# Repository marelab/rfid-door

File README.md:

# ESP8266 RFID - Access Control with Wiegand Protocol powerd by Door Bell transformer 8-12V AC or DC

## First of all 
big thanks to the [ESP-RFID Project](https://github.com/esprfid/esp-rfid) with the work they have done. The "rfid-door" hardware is 100% compatible with their software also a modified [Firmware](https://github.com/marelab/esp-rfid/releases) with extended MQTT support is included with the marelab RFID-DOOR Version that can be used. Just the hardware design is differnt in my version. The RFID-DOOR pcb is designed to be powered directly from the AC Ring Bell transformer (8-12V AC). But can also be configured to use a 8-12V DC power by just solder bridges. Main reason why I used a different design was the fact that I didn't wanted to setup a new DC source and cables for that device, it can be integrated without any extra power infrastructure. Most german households have a AC Ringbell with 8 or 12V transformer next to the door. 

## RFID-DOOR
 
 NFC/RFID WIFI Access Control hardware interfacing a cheap MFRC522, PN532 RFID, RDM6300 readers or Wiegand RFID readers with a Espressif's ESP8266 Microcontroller as Wifi Bridge to drive the door open coil to unlock a home door and to include it into a home automatisation system. The pcb is designed with [KiCad](http://kicad.org/) an opensoure EDA System. Ready Gerber Files can be found under Gerber. Plz use the Version Tab for download the newest Release the Master Branch includes the current development stage! 

## Differnces of the ESP-RFID Hardware to RFID-DOOR Hardware
The marelab RFID-DOOR hardware: 
```
* Can be powered by AC RingBell transformer directly no seperate power source need at the installation spot
* No mechanical Relais just Silicon Door coil is driven by smal opto mosfet
* Currentlimitation of the door coil to limit the current breakdown while magentic lock is activated  
* 5V kompatible Wiegand DO/D1 Lines as default
```

## Features
### For Users
* Minimal effort for setting up your Access Control system, just flash and everything can be configured via Web UI
* Capable of managing up to 1.000 Users (even more is possible)
* Great for Maker Spaces, Labs, Schools, etc
* Cheap to build and easy to maintain
### For Tinkerers
* Open Source (minimum amount of hardcoded variable, this means more freedom)
* Using WebSocket protocol to exchange data between Hardware and Web Browser
* Data is encoded as JSON object
* Records are Timestamped (Time synced from a NTP Server)
* MQTT enabled for using by Smart Home automatisation.
* Bootstrap, jQuery, FooTables for beautiful Web Pages for both Mobile and Desktop Screens
* Thanks to ESPAsyncWebServer Library communication is Asynchronous
### Official Hardware
* Small size form factor just 4,5cm * 4,5 cm
* Single power source (Ring Bell transformer) for RFID-DOOR hardware & RFID Wiegand Reader and magnetic lock for opening doors.
* Exposed programming pins for ESP8266
* Regarding hardware design, you get multiple possible setup options:
* Forward Bell ringing on reader to MCU or pass it out of board
* Control reader’s status LED
* Control reader’s status BUZZER sound *
* Power reader, lock and the board through single 8V, AC Ring Bell Transformer
* Power for Magnetic Lock / Door Relais is supplied by RFID-DOOR Hardware
* Possible to use any kind and any type of Wiegand readers
* Smart Home integration over MQTT
* Fits in an universal enclosures with DIN mount
* Open Source Hardware

## Getting Started
New features (and also bugs) are introduced often and some functions may become deprecated. Please feel free to comment or give feedback.

### Standard Door Bell Setup

### RFID-DOOR integrated into Door Bell Setup

## Hardware you need

### Hardware
* [marelab RFID-DOOR Board](https://www.marelab.org/index.php/smarthome-iot/rfid-door) can be ordered here
* A MFRC522 RFID PCD Module or PN532 NFC Reader Module or RDM6300 125KHz RFID Module Wiegand based RFID reader
* n quantity of Mifare Classic 1KB (recommended due to available code base) PICCs (RFID Tags) equivalent to User Number
* A door Relay 8-12V
* A Ringbell Transformer 8-12V 

### Software you need
* Get the latest hardware release from [here.](https://github.com/marelab/rfid-door/releases)
* Get the firmware software from [here.](https://github.com/marelab/esp-rfid/releases)
* See Building [Building](https://github.com/marelab/rfid-door#building)
* See [Security](https://github.com/marelab/esp-rfid#security) for your safety.
* See [ChangeLog](https://github.com/marelab/esp-rfid/blob/dev/CHANGELOG.md)

### Setup & get it running 
* First, flash firmware (you can use /bin/flash.bat on Windows) to your ESP either using Arduino IDE or with your favourite flash tool
* (optional) Fire up your serial monitor to get informed
* Search for Wireless Network "esp-rfid-xxxxxx" and connect to it (It should be an open network and does not require password)
* Open your browser and type either "http://192.168.4.1" or "http://esp-rfid.local" (.local needs Bonjour installed on your computer) on address bar.
* Log on to ESP, default password is "admin"
* Go to "Settings" page
* Configure your amazing access control device. Push "Scan" button to join your wireless network, configure RFID hardware, Relay Module.
* Save settings, when rebooted your ESP will try to join your wireless network.
* Check your new IP address from serial monitor and connect to your ESP again. (You can also connect to "http://esp-rfid.local")
* Go to "Users" page
* Scan a PICC (RFID Tag) then it should glimpse on your Browser's screen.
* Type "User Name" or "Label" for the PICC you scanned.
* Choose "Allow Access" if you want to
* Click "Add"
* Congratulations, everything went well, if you encounter any issue feel free to ask help on GitHub.

### RFID-DOOR Connectors

| Number | Function                                     | ESP8266           |
|-------:|:--------------------------------------------:|:------------------|
| 1      | DoorR / Magnetic Look / Door Relais Conector |    -              |
| 2      | DoorR / Magnetic Look / Door Relais Conector |    -              |
| 3      | 12V out / 12V+ DC                            |    -              |
| 4      | D0 Wiegand D0                                | GPIO-04*          |
| 5      | D1 Wiegand D1                                | GPIO-05*	        |
| 6      | LED                                          | GPIO-05           |
| 7      | W26                                          | GPIO-05           |
| 8      | BUZ                                          | GPIO-05           |
| 9      | GND                                          |    -              |
| 10     | GND                                          |    -              |
| 11     | 12V AC                                       |    -              |
| 12     | 12V AC                                       |    -              |
| 13     | JP4 Reset                                    | GPIO-05           |
| 14     | JP5 Firmware Upload enable                   | GPIO-05           |
|        | JP3-1 3,3V Serial Connector to ESP8266       |                   |
|        | JP3-2 TX Serial Connector to ESP8266         | GPIO-05           |
|        | JP3-3 RX Serial Connector to ESP8266         | GPIO-05           |
|        | JP3-4 GND Serial Connector to ESP8266        | GPIO-05           |

(*) 5V In/Output Signal

### RFID-DOOR Functional Blocks

| Letter | Hardware Function Block                                                                                             | 
|-------:|:-------------------------------------------------------------------------------------------------------------------:|
| A      | Switches the Magnetic Lock/Door Relais by Opto Mosfet and 2W Magnetic Lock Resistor that limits starting current    |
| B      | 3,3V Linear Driver for ESP8266 supply                                                                               | 
| C      | Diode Bridge & Self Resetable Fuse for converting AC to DC Ripple power. The Cxx Cap is decoupled by a the Diode Dxx if the 12V of the Bridge falls down for ms while the magnetic lock is used it delivers the energy for the 5V stage  | 
| D      | 5V StepDown Converter that powers (B) and the MosFet for (E)                                                        | 
| E      | In / Out 3,3V Signal Lines ESP to 5V on Conector 

## **Building** & Setup Hardware

#### The AC Ring Bell Transformer
Be carefull with 12V AC Ring bell transformers. The DC Voltage after the Diode bridge can be around 18V DC!!! That will not kill the RFID-DOOR hardware but it will kill a 12V RFID Reader that is connected to the RFID-DOOR. Why is that happening most Readers have a build in AMS1117 Voltage regulator wich has a maximum 16V input. The RFID-DOOR transforms the AC input Voltage in three stages first Stage is a diode bridge to transform AC to rippled DC then a Step Down Regulator generates 5V DC that can handle 24V DC input next the 5V is converted to 3,3V with a AMS1117 for the ESP. The RFID-DOOR won't get killed because the AMS1117 lives behind the 5V StepDown stage. The Rippled DC is connected directly to the power reader connectors. 
The easiest way to get around that problem is using a 8V AC Ringbell transformer. For example someting like this:

Just use the 8V instead of 12V. The rippled DC after the Diode Bridge is around 14-15V and in the range a AMS1117 of the Reader can handle.
Just for details about german standard and regulations for the bell transformer that has to be used. https://de.wikipedia.org/wiki/Klingeltransformator

####  Placing the ACT4088 IC
The ACT4088 Step Down is a quite tiny part and its quite inpossible to indetify Pin1 without a mircoscope or strong lense. As hint thats a picture of the ACT4088 to find Pin1 as marked in the image.

#### Cad drawing 

The Encloser drill holes dimension is 2,5 mm

#### Special Configuration solder bridges
The board can be customized for special needs if you don't want or have a standard configuration. Some solder Bridges see the pictures of the PCB Back & Top where to find them can configure direct 12V DC Input and or disable the 5V Stage for the D0 / D1 pins. 

!!!Warning all described here might disable some safety features of the board so you should totaly know what you are doing using this!!!

```
##### 12V DC Power Input
If your power source is 12V DC you don't need the Diode Bridge and the 
Capacitor Cxx to be soldered on the board. Solder the JP1 and JP2 
Solder Bridge Jumpers  
```

```
##### 3,3V DO / D1 Wiegand Interface
If you don't need a 5V TTL compatble In/Out of the D1/D0 Lines just 
solder the Solder Bridges JP7/JP8. Don't solder then the Mosfets Q1 & 
Q2 as well as the four Resistors Rxx,Rxx,Rxx,Rxx. 
```

```
##### Bridge the Magnetic Lock / Door Relais current limitation 
By solder the JP3 Bridge the R1 2W Resistor is bridged and so no current 
limitation of a starting magentic coil / Door Lock saves the MosFet!!! 
The R1 Resitor don't need to be solderd anymore. 
```

## Software

#### Wich firmware should I use?
If you want to have a smart home integration or want to manage more then one Door I would recomend the marelab version, because of the extended MQTT functions and multi device support.
Otherwise you can use also the orginal firmware from the ESP-RFID Project. 

#### Using Compiled Binaries
Download compiled binaries from GitHub Releases page:
marelab modified firmware with extended MQTT support https://github.com/marelab/esp-rfid/releases 
or the orignal firmware from https://github.com/esprfid/esp-rfid/releases

#### Flashing the device
For a selfmade NF-DOOR pcb you need a USB to serial Bridge to flash the first Version. New Firmware Versions can then be updated by OTA (Over the Air Wifi Update) done with the web gui.
If you bought the RFID-DOOR Hardware the ESP is already programmed with the firmware so you don't need the USB to serial adapter for flashing.
On Windows you can use **"flash.bat"**, it will ask you which COM port that ESP is connected and then flashes it. You can use any flashing tool and do the flashing manually. The flashing process itself has been described at numerous places on Internet.

#### Self building With PlatformIO
##### Backend
The build environment is based on [PlatformIO](http://platformio.org). Follow the instructions found here: http://platformio.org/#!/get-started for installing it but skip the ```platform init``` step as this has already been done, modified and it is included in this repository. In summary:

```
sudo pip install -U pip setuptools
sudo pip install -U platformio
git clone https://github.com/esprfid/esp-rfid.git
cd esp-rfid
platformio run
```

When you run ```platformio run``` for the first time, it will download the toolchains and all necessary libraries automatically.

##### Debug information
When you compiling and flashing a debug Version the ESP sends Debug Messages over the Serial Port thats usefull for trace and test purpose.

##### Useful commands:

* ```platformio run``` - process/build all targets
* ```platformio run -e generic -t upload``` - process/build and flash just the ESP12e target 
* ```platformio run -e debug -t upload``` - process/build and flash just the ESP12e target 
* ```platformio run -t clean``` - clean project (remove compiled files)

The resulting (built) image(s) can be found in the directory ```/bin``` created during the build process.

##### Frontend
You can not simply edit Web UI files because you will need to convert them to C arrays, which can be done automatically by a gulp script that can be found in tools directory or you can use compiled executables at the same directory as well (for Windows PCs only).

If you want to edit esp-rfid's Web UI you will need (unless using compiled executables):
* NodeJS
* npm (comes with NodeJS installer)
* Gulp (can be installed with npm)

Gulp script also minifies HTML and JS files and compresses (gzip) them. 

In order to test your changes without flashing the firmware you can launch websocket emulator which is included in tools directory.
* You will need to Node JS for websocket emulator.
* Run ```npm update``` to install dependencies
* Run emulator  ```node wserver.js```
* then you will need to launch your browser with CORS disabled:
* ```chrome.exe --args --disable-web-security -–allow-file-access-from-files --user-data-dir="C:\Users\USERNAME"```

Get more information here: https://stackoverflow.com/questions/3102819/disable-same-origin-policy-in-chrome

### Pin Layout

The following table shows the typical pin layout used for connecting readers hardware to ESP:

| ESP8266 | NodeMcu/WeMos | Wiegand | PN532 | MFRC522 | RDM6300 | 
|--------:|:-------------:|:-------:|:-----:|:-------:|:-------:|
| GPIO-15 | D8            |         | SS    | SDA/SS  |         |
| GPIO-13 | D7            | D0      | MOSI  | MOSI    |         |
| GPIO-12 | D6            | D1      | MISO  | MISO    |         |
| GPIO-14 | D5            |         | SCK   | SCK     | TX      |
| GPIO-04 | D2            |         |       |         |         |
| GPIO-05 | D1            |         |       |         |         |

For Wiegand based readers, you can configure D0 and D1 pins via settings page. By default, D0 is GPIO-4 and D1 is GPIO-5

## Time
We are syncing time from a NTP Server (in Client -aka infrastructure- Mode). This will require ESP to have an Internet connection. Additionally your ESP can also work without Internet connection too (Access Point -aka Ad-Hoc- Mode),  without giving up functionality.
This will require you to do syncing manually. ESP can store and hold time for you approximately 51 days without a major issue, device time can drift from actual time depending on usage, temperature, etc.
So you have to login to settings page and sync it in a timely fashion.

## **Security**
We assume **ESP-RFID** project -as a whole- does not offer strong security. There are PICCs available that their UID (Unique Identification Numbers) can be set manually (Currently esp-rfid relies only UID to identify its users). Also there may be a bug in the code that may result free access to your belongings. And also, like every other network connected device esp-rfid is vulnerable to many attacks including Man-in-the-middle, Brute-force, etc.

This is a simple, hobby grade project, do not use it where strong security is needed.

What can be done to increase security? (by you and by us)

* We are working on more secure ways to Authenticate RFID Tags.
* You can disable wireless network to reduce attack surface. (This can be configured in Web UI Settings page)
* Choose a strong password for the Web UI

## Scalability
Since we are limited on both flash and ram size things may get ugly at some point in the future. You can find out some test results below.

## License
The code parts are licensed under [MIT License](https://github.com/esprfid/esp-rfid/blob/stable/LICENSE), 3rd party libraries that are used by this project are licensed under different license schemes, please check them out as well.

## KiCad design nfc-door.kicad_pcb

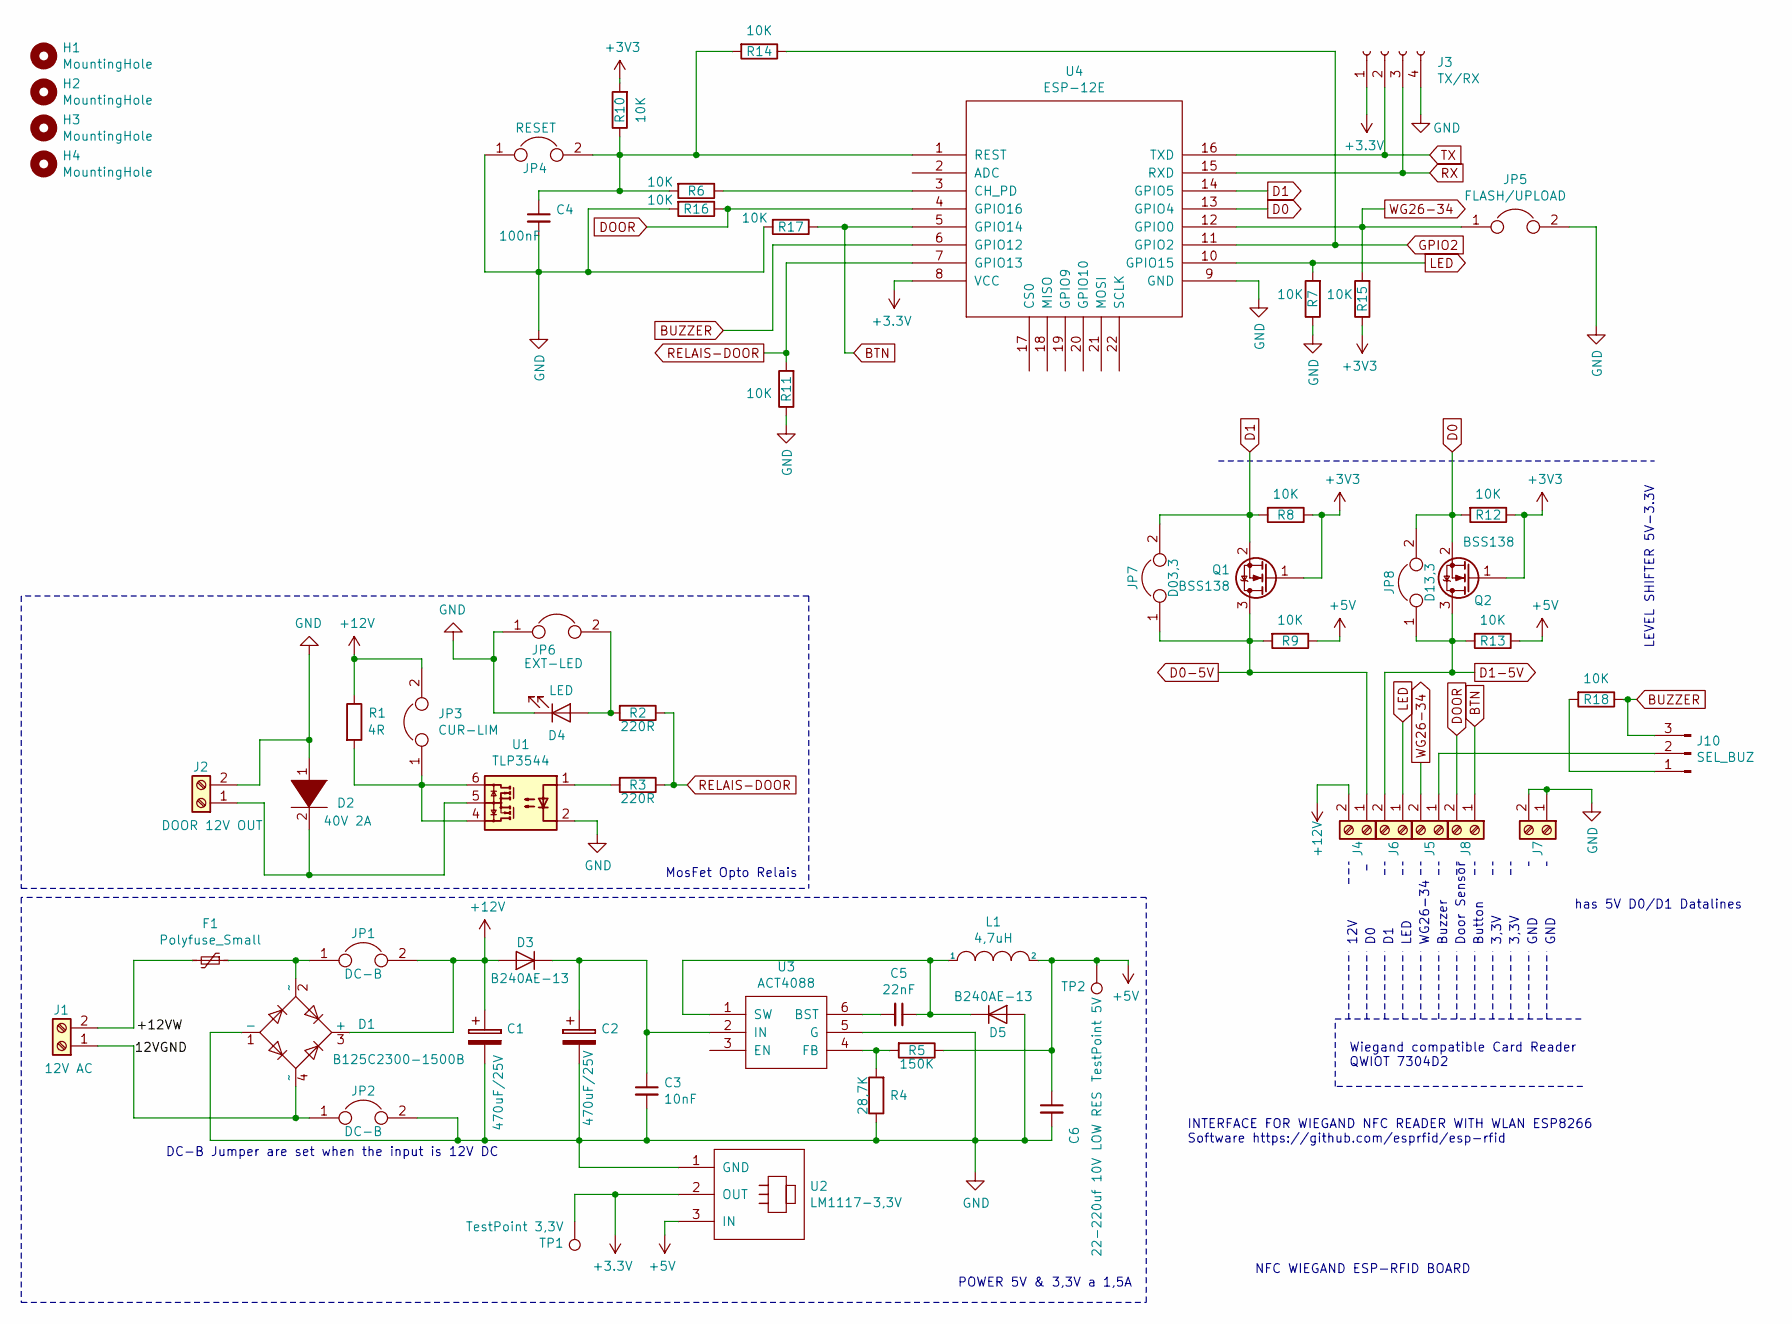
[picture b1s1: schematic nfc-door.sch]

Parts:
C1, C2: 470uF/25V; CP_Radial_D10.0mm_P5.00mm
C3: 10nF; C_0805
C4: 100nF; C_0805
C5: 22nF; C_0805
C6: 22-220uf 10V LOW RES; C_1206
D1: B125C2300-1500B; Diode_Bridge_Round_D8.9mm
D2: 40V 2A; D_1206
D3, D5: B240AE-13; D_SMA_Handsoldering
D4: LED; LED_0805
F1: Polyfuse_Small; Fuse_SMD2920
H1, H2, H3, H4: MountingHole; MountingHole_2.5mm_Pad
J1: 12V AC; RM3.5-CON
J2: DOOR 12V OUT; RM3.5-CON
J3: TX/RX; Pin_Header_Straight_1x04_Pitch2.54mm
J4, J5, J6, J7, J8: RM3.5-CON
J10: SEL_BUZ; Pin_Header_Straight_1x03_Pitch2.54mm
JP1, JP2: DC-B; SolderBridge
JP3: CUR-LIM; SolderBridge
JP4: RESET; Pin_Header_Straight_1x02_Pitch2.54mm
JP5: FLASH/UPLOAD; Pin_Header_Straight_1x02_Pitch2.54mm
JP6: EXT-LED; Pin_Header_Straight_1x02_Pitch2.54mm
JP7: D03,3; SolderBridge
JP8: D13,3; SolderBridge
L1: 4,7uH; Inductor_Taiyo-Yuden_NR-40xx_HandSoldering
Q1, Q2: BSS138; SOT-23
R1: 4R; R_2512_HandSoldering
R2, R3: 220R; R_1206
R4: 28,7K; R_1206
R5: 150K; R_1206
R6, R7, R8, R9, R10, R11, R12, R13, R14, R15, R16, R17, R18: 10K; R_1206
TP1: TestPoint 3,3V; SolderWirePad_single_0-8mmDrill
TP2: TestPoint 5V; SolderWirePad_single_0-8mmDrill
U1: TLP3544; DIP-6_W7.62mm_LongPads
U2: LM1117-3,3V; Pin_Header_Straight_1x03_Pitch2.54mm
U3: ACT4088; SOT-23-6
U4: ESP-12E; ESP-12E_SMD

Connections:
+5V: C6.1, L1.2, R5.1, R9.1, R13.1, TP2.1, U2.3 (IN)
+12V: C1.1, D1.3 (+), D3.2 (A), J4.2, JP1.2, JP3.2, R1.1
BTN: J8.1, R17.1, U4.5 (GPIO14)
BUZZER: J10.3, R18.1, U4.6 (GPIO12)
D0: JP8.2, Q2.2 (S), R12.2, U4.13 (GPIO4)
D0-5V: J4.1, JP7.1, Q1.3 (D), R9.2
D1: JP7.2, Q1.2 (S), R8.2, U4.14 (GPIO5)
D1-5V: J6.2, JP8.1, Q2.3 (D), R13.2
DOOR: J8.2, R16.1, U4.4 (GPIO16)
GND: C1.2, C2.2, C3.2, C4.2, C6.2, D1.1 (-), D2.1 (K), D4.1 (K), D5.2 (A), J2.2, J3.4, J7.1, J7.2, JP2.2, JP4.1, JP5.2, JP6.1, R4.1, R7.1, R11.1, R16.2, R17.2, U1.2, U2.1 (GND), U3.5 (G), U4.9 (GND)
GPIO2: R14.1, U4.11 (GPIO2)
LED: J6.1, R7.2, U4.10 (GPIO15)
unnamed: C2.1, C3.1, D3.1 (K), U3.2 (IN)
unnamed: C4.1, JP4.2, R6.2, R10.1, R14.2, U4.1 (REST)
unnamed: C5.1, D5.1 (K), L1.1, U3.1 (SW)
unnamed: C5.2, U3.6 (BST)
unnamed: D1.2 (~~), F1.1, JP1.1
unnamed: D1.4 (~~), J1.1, JP2.1
unnamed: D2.2 (A), J2.1, U1.5
unnamed: D4.2 (A), JP6.2, R2.2
unnamed: F1.2, J1.2
unnamed: J10.1, R18.2
unnamed: J5.1, J10.2
unnamed: JP3.1, R1.2, U1.4, U1.6
unnamed: R3.2, U1.1
unnamed: R4.2, R5.2, U3.4 (FB)
unnamed: R6.1, U4.3 (CH_PD)
RELAIS-DOOR: R2.1, R3.1, R11.2, U4.7 (GPIO13)
RX: J3.3, U4.15 (RXD)
TX: J3.2, U4.16 (TXD)
WG26-34: J5.2, JP5.1, R15.2, U4.12 (GPIO0)

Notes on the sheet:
Wiegand compatible Card Reader QWIOT 7304D2
GND
12V
has 5V D0/D1 Datalines
LEVEL SHIFTER 5V-3.3V
NFC WIEGAND ESP-RFID BOARD
INTERFACE FOR WIEGAND NFC READER WITH WLAN ESP8266 Software https://github.com/esprfid/esp-rfid
DC-B Jumper are set when the input is 12V DC
POWER 5V & 3,3V a 1,5A
MosFet Opto Relais
LED
WG26-34
Buzzer
Door Sensor
Button
3,3V
GND

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
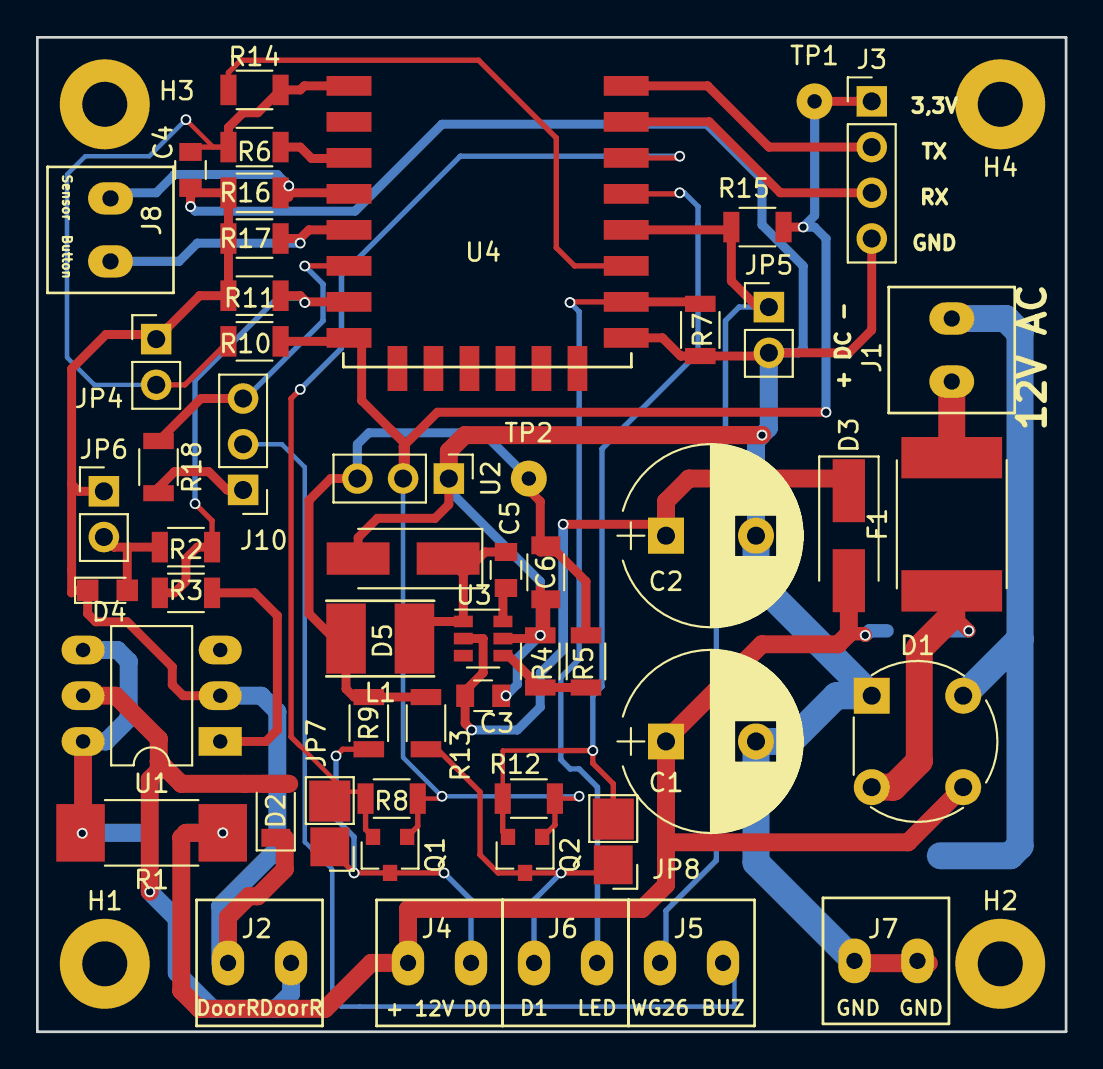
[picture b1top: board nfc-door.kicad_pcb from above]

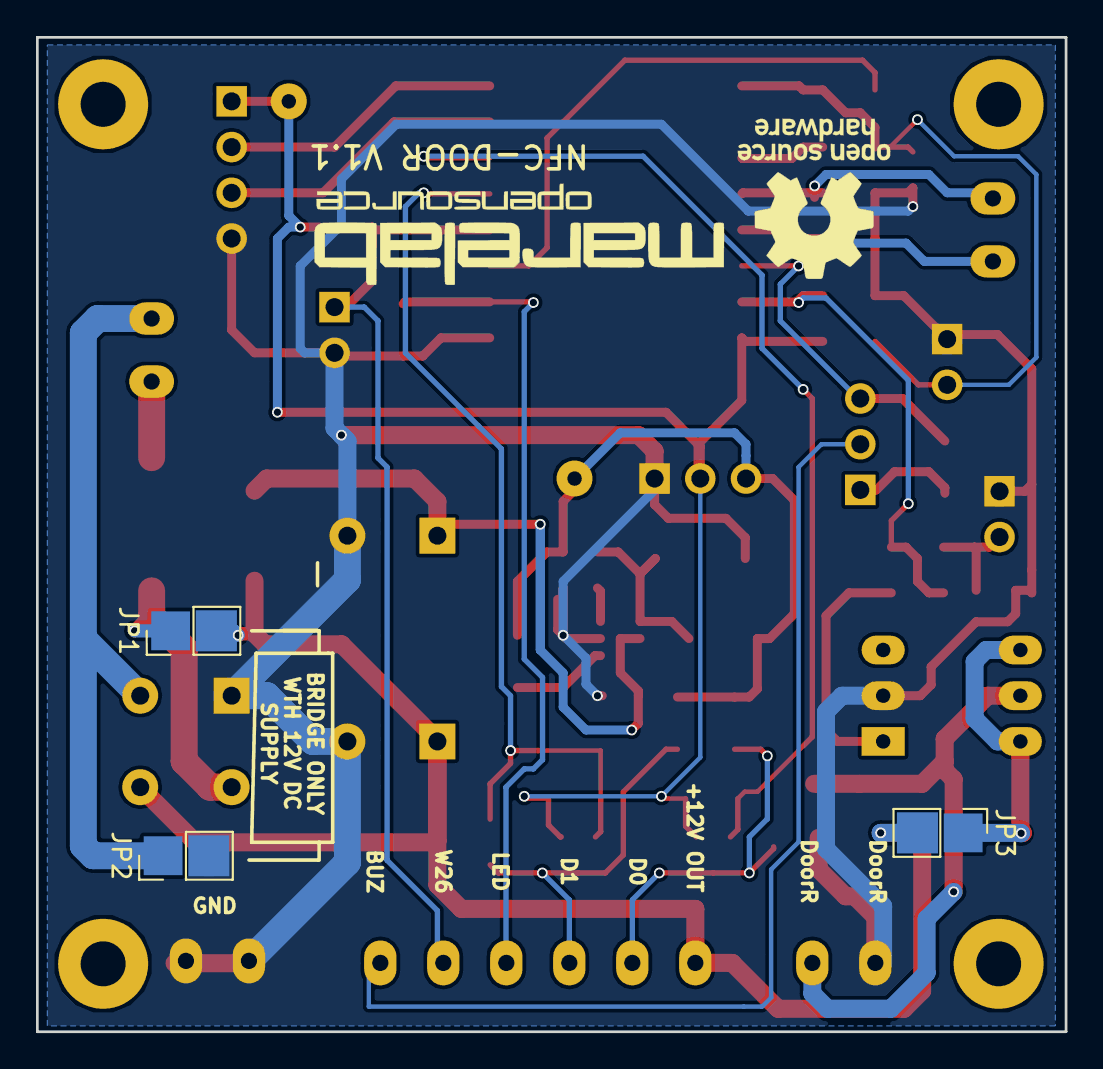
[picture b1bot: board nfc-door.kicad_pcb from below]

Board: 2 copper layers, 57.2 x 55.2 mm, 60 parts (3 on the bottom side), 32 nets.

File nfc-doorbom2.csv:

Pos;Description;Part;Name;Wert;Footprint;Quantity Per PCB;Datasheet;manf-num
1;;C_Small;C4;100nF;C_0805;1;https://www.mouser.de/ProductDetail/Murata-Electronics/GCM21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;CC0805KPX7R8BB104
2;;C_Small;C3;10nF;C_0805;1;;CC0805KRX7R8BB103
3;;C_Small;C6;22-220uf 10V LOW RES ;C_1206;1;;CC0805JRX7R8BB223
4;;C_Small;C5;22nF;C_0805;1;;CC0805JRX7R8BB223
5;Polarized capacitor;CP;C1 C2;470uF/25V;CP_Radial_D10.0mm_P5.00mm;2;https://www.mouser.de/datasheet/2/212/KEM_A4074_ESL-1128319.pdf;ESL477M025AH9
6;Diode symbol for simulation only. Pin order incompatible with official kicad footprints;DIODE;D2; 40V 2A ;D_1206;1;https://www.mouser.de/ProductDetail/AVX/SD1206T040S2R0?qs=sG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;SD1206T040S2R0
7;Silicon Bridge Rectifier, 125V Vrms, 1.5A If, pins=-A+A, SIL-package;B125C2300-1500B;D1;B125C2300-1500B;Diode_Bridge_Round_D8.9mm;1;https://diotec.com/tl_files/diotec/files/pdf/datasheets/b40c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;
8;Diode;D;D3 D5;B240AE-13;D_SMA_Handsoldering;2;https://www.mouser.de/datasheet/2/115/B220AEBE-B245AEBE-1115122.pdf;B240AE-13
9;Light emitting diode;LED;D4;LED;LED_0805;1;~;
10;Resettable fuse, polymeric positive temperature coefficient, small symbol;Polyfuse_Small;F1;Polyfuse_Small;Fuse_SMD2920;1;https://www.mouser.de/ProductDetail/Bel-Fuse/0ZCF0200AF2C?qs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;0ZCF0200AF2C
11;Generic screw terminal, single row, 01x02;Screw_Terminal_01x02;J4 J5 J6 J7 J8;;RM3.5-CON;5;~;
12;Generic screw terminal, single row, 01x02;Screw_Terminal_01x02;J1;12V AC;RM3.5-CON;1;~;
13;Generic screw terminal, single row, 01x02;Screw_Terminal_01x02;J2;DOOR 12V OUT;RM3.5-CON;1;~;
14;Generic connector, single row, 01x03, script generated (kicad-library-utils/schlib/autogen/connector/);Conn_01x03_Male;J10;SEL_BUZ;Pin_Header_Straight_1x03_Pitch2.54mm;1;~;
15;Generic connector, single row, 01x04, script generated (kicad-library-utils/schlib/autogen/connector/);Conn_01x04_Female;J3;TX/RX;Pin_Header_Straight_1x04_Pitch2.54mm;1;~;
16;Jumper, normally closed;Jumper;JP3;CUR-LIM;SolderBridge;1;~;
17;Jumper, normally closed;Jumper;JP7;D03,3;SolderBridge;1;~;
18;Jumper, normally closed;Jumper;JP8;D13,3;SolderBridge;1;~;
19;Jumper, normally closed;Jumper;JP1 JP2;DC-B;SolderBridge;2;~;
20;Jumper, normally closed;Jumper;JP6;EXT-LED;Pin_Header_Straight_1x02_Pitch2.54mm;1;~;
21;Jumper, normally closed;Jumper;JP5;FLASH/UPLOAD;Pin_Header_Straight_1x02_Pitch2.54mm;1;~;
22;Jumper, normally closed;Jumper;JP4;RESET;Pin_Header_Straight_1x02_Pitch2.54mm;1;~;
23;Capacitor symbol for simulation only;INDUCTOR;L1;4,7uH;Inductor_Taiyo-Yuden_NR-40xx_HandSoldering;1;SRN4026-4R7M;SRN4026-4R7M
24;50V Vds, 0.22A Id, N-channel MOSFET, SOT-23;BSS138;Q1 Q2;BSS138;SOT-23;2;https://www.fairchildsemi.com/datasheets/BS/BSS138.pdf;BSS138
25;;R;R6 R7 R8 R9 R10 R11 R12 R13 R14 R15 R16 R17 R18;10K;R_0805;13;;
26;;R;R5;150K;R_1206;1;;
27;;R;R2 R3;220R;R_1206;2;;
28;;R;R4;28,7K;R_1206;1;;
29;;R;R1;4R;R_2512_HandSoldering;1;https://www.mouser.de/ProductDetail/TE-Connectivity-Neohm/CR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;
30;5V StepDown Wandler;ACT4088;U3;ACT4088;SOT-23-6;1;;ACT4088US-T
31;ESP8266 ESP-12E module, 22 pins, 2mm, PCB antenna;ESP-12E;U4;ESP-12E;ESP-12E_SMD;1;http://l0l.org.uk/2014/12/esp8266-modules-hardware-guide-got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;
32;3,3V 1.5A CHINA MODUL;LM1117-3,3V;U2;LM1117-3,3V;Pin_Header_Straight_1x03_Pitch2.54mm;1;;
33;Photo MOSFET optically coupled, ON 3.5A, 60mohm, OFF state 40V, Isolation 2500 VRMS, DIP-6;TLP3544;U1;TLP3544;DIP-6_W7.62mm_LongPads;1;https://toshiba.semicon-storage.com/info/docget.jsp?did=1266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;TLP3544(F)

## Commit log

2019-05-03 Initial V1.1 Version
2019-05-03 Starting ReadMe.md
2019-05-04 Init Version
2019-05-04 overview NFC-DOOR install
2019-05-04 Graphic added
2019-05-14 V1.1 Version
    Version V1.1
    * Corrected Diode Bridge
    * 1206 22uF CAP
2019-05-16 Update Cleaned up Repro
2019-05-16 Schematic & 3D png/pdf
2019-05-16 ACT4088 oriantation
2019-05-16 Update Release
2019-05-16 Firmware to choose from
2019-05-16 Changes to links
2019-05-16 Adding debug build info
2019-05-16 Update Description
2019-05-16 Added pcb pic
2019-05-16 Basic & RFID Setup Grafic
2019-05-16 Images standard & NFC-DOOR setup
2019-05-17 renaming to rfid-door
2019-05-17 Update and grafics Connectors & Overview
2019-05-17 Added Connector Table
2019-05-17 Added Top & Back PCB images
2019-05-17 Special Configuration over Solder Bridges
2019-05-17 Added Demension grafic
2019-05-17 Some cleanUp
2019-05-17 Logo grafics added
2019-05-17 update logo
2019-05-17 Logo update
2021-11-08 Update README.md
    https://forum.kicad.info/t/warning-avoid-all-links-to-kicad-pcb-org-use-kicad-org/31521

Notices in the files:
README.md:
License:
The code parts are licensed under [MIT License](https://github.com/esprfid/esp-rfid/blob/stable/LICENSE), 3rd party libraries that are used by this project are licensed under different license schemes, please check them out as well.
